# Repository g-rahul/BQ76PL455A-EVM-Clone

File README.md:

# BQ76PL455A-EVM-Clone
This respository contains low cost design files for BQ76PL455A-EVM Clone.

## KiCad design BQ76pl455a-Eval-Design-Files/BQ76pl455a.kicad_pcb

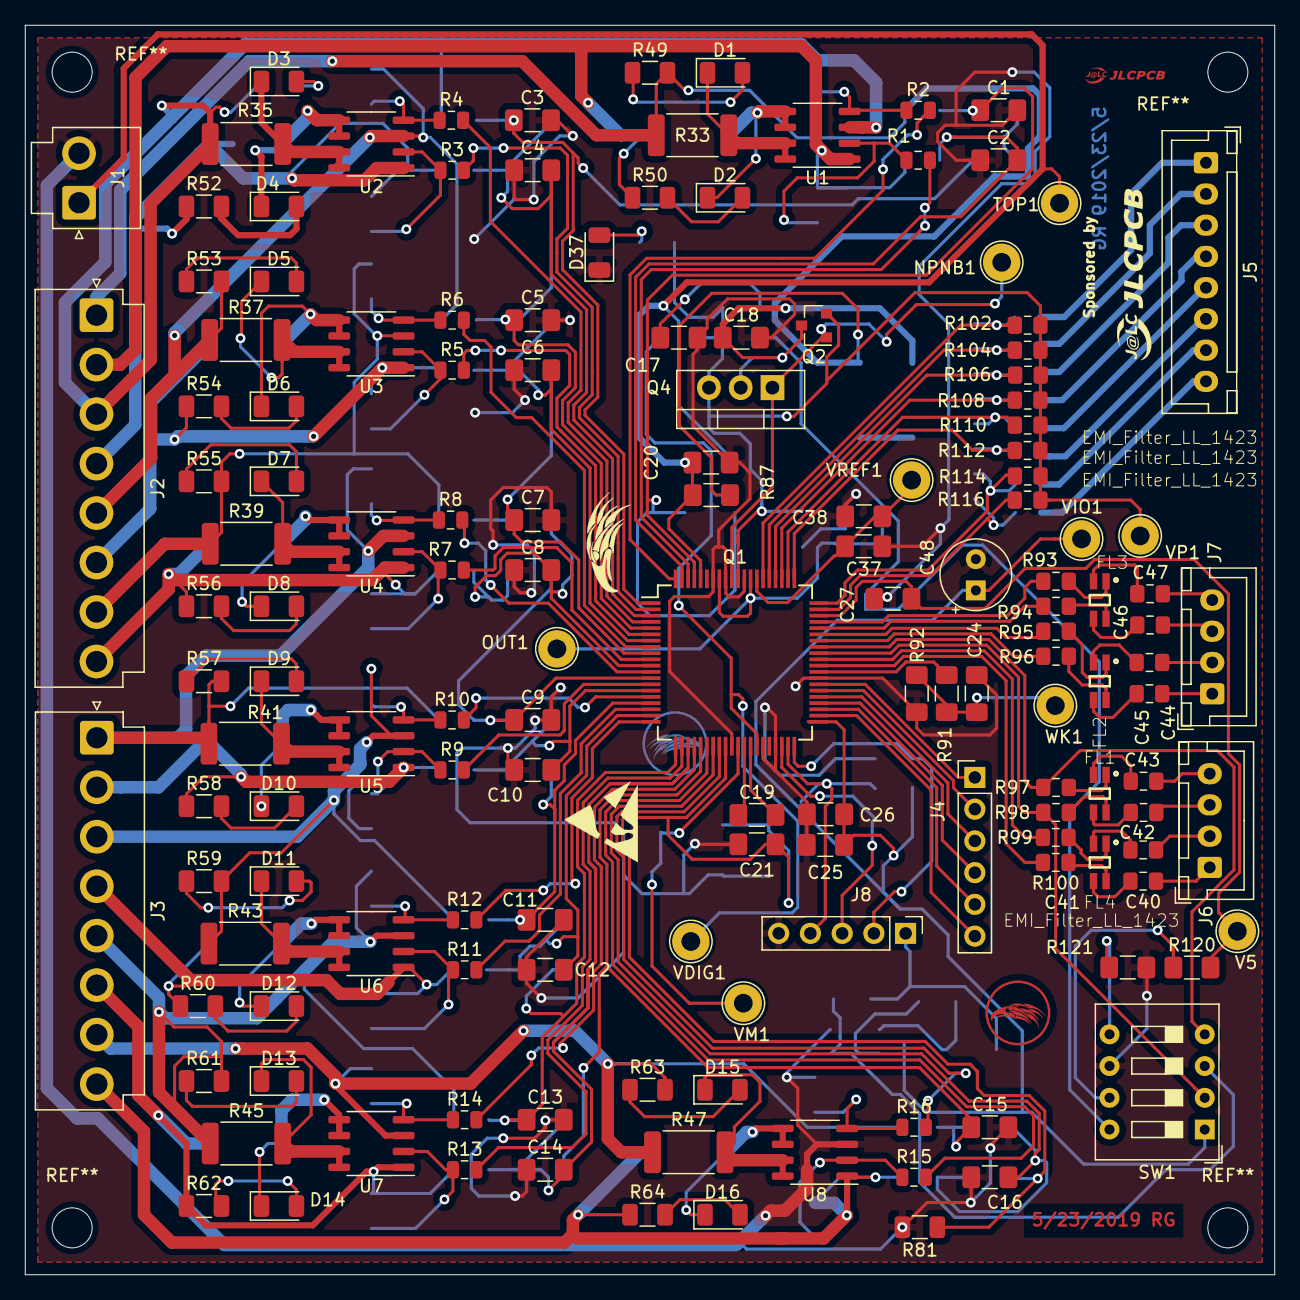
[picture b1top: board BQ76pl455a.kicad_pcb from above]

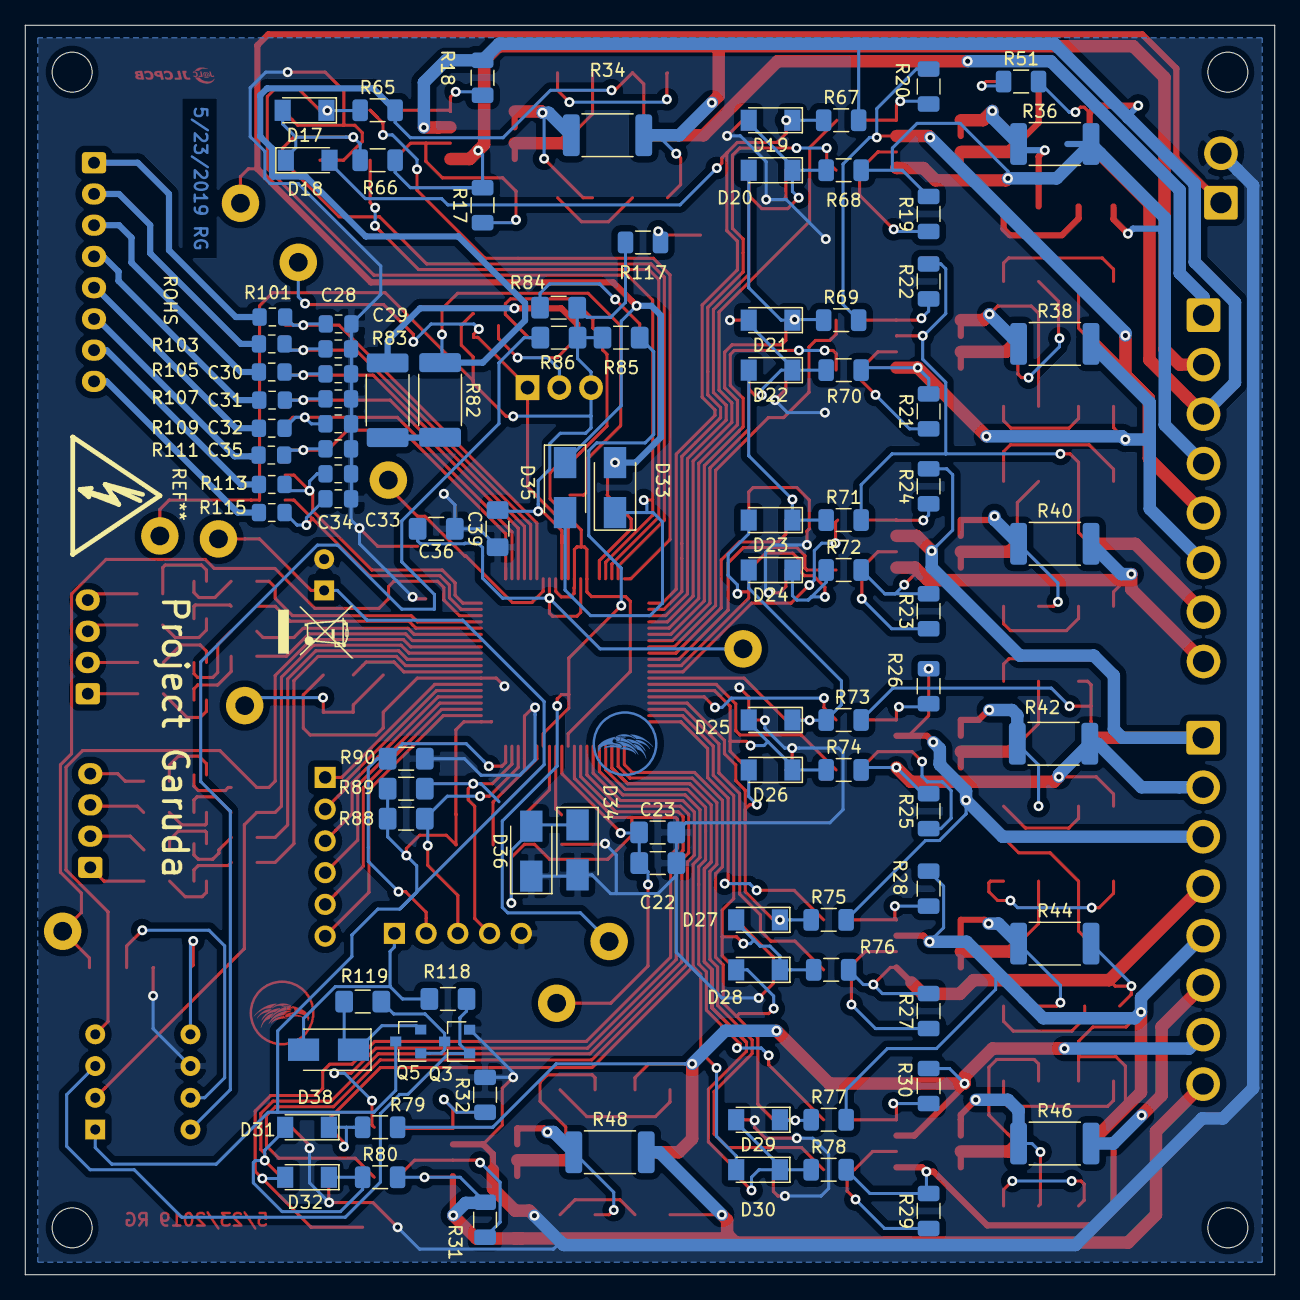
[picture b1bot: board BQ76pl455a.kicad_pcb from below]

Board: 2 copper layers, 100.0 x 100.0 mm, 243 parts (95 on the bottom side), 179 nets.

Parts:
C1, C2, C3, C4, C5, C6, C7, C8, C9, C10, C11, C12, C13, C14, C15, C16: C_Small; C_1206_3216Metric_Pad1.42x1.75mm_HandSolder
C17, C27: 4.7uF; C_1206_3216Metric_Pad1.42x1.75mm_HandSolder
C18, C19, C20, C21: 1uF; C_1206_3216Metric_Pad1.42x1.75mm_HandSolder
C22, C23: C; C_1206_3216Metric_Pad1.42x1.75mm_HandSolder
C24, C25, C26, C37, C38, C39: 0.1uF; C_1206_3216Metric_Pad1.42x1.75mm_HandSolder
C28, C29, C30, C31, C32, C33, C34, C35, C40, C41, C42, C43, C44, C45, C46, C47: 0.1uF; C_0805_2012Metric_Pad1.15x1.40mm_HandSolder
C36: 395pF; C_1206_3216Metric_Pad1.42x1.75mm_HandSolder
C48: CP; CP_Radial_Tantal_D5.5mm_P2.50mm
D1, D2, D3, D4, D5, D6, D7, D8, D9, D10, D11, D12, D13, D14, D15, D16, D37: LED; LED_1206_3216Metric
D17, D18, D19, D20, D21, D22, D23, D24, D25, D26, D27, D28, D29, D30, D31, D32: D_Zener_Small_ALT; D_MiniMELF
D33, D34, D35, D36, D38: MRA4007T3G; D_SMA
FL1, FL2, FL3, FL4: EMI_Filter_LL_1423; IND_744232090
J1: Conn_01x02_Male; JST_VH_B2P-VH-B_1x02_P3.96mm_Vertical
J2, J3: Conn_01x08_Male; JST_VH_B8P-VH-B_1x08_P3.96mm_Vertical
J4: Conn_01x06_Male; PinHeader_1x06_P2.54mm_Vertical
J5: Conn_01x08_Male; JST_XH_B8B-XH-A_1x08_P2.50mm_Vertical
J6, J7: Conn_01x04_Male; JST_XH_B4B-XH-A_1x04_P2.50mm_Vertical
J8: Conn_01x05_Male; PinHeader_1x05_P2.54mm_Vertical
NPNB1: TestPoint; TestPoint_Loop_D2.54mm_Drill1.5mm_Beaded
OUT1: TestPoint; TestPoint_Loop_D2.54mm_Drill1.5mm_Beaded
Q1: BQ76PL455A; TQFP-80_12x12mm_P0.5mm
Q2: MMBT5550L; SOT-23
Q3: ZXMN6A07F; SOT-23
Q4: MJE13007G; TO-220-3_Vertical
Q5: Si2319CDS; SOT-23
R1, R2, R3, R4, R5, R6, R7, R8, R9, R10, R11, R12, R13, R14, R15, R16: 2k; R_0805_2012Metric
R17, R18, R19, R20, R21, R22, R23, R24, R25, R26, R27, R28, R29, R30, R31, R32: 10k; R_1206_3216Metric
R33, R34, R35, R36, R37, R38, R39, R40, R41, R42, R43, R44, R45, R46, R47, R48: 10e; R_2512_6332Metric
R49, R50, R51, R52, R53, R54, R55, R56, R57, R58, R59, R60, R61, R62, R63, R64, R65, R66, R67, R68, R69, R70, R71, R72, R73, R74, R75, R76, R77, R78, R79, R80, R81, R117: 100; R_1206_3216Metric
R82, R83: 200; R_2512_6332Metric_Pad1.52x3.35mm_HandSolder
R84, R85, R86: 1; R_1206_3216Metric_Pad1.42x1.75mm_HandSolder
R87, R88, R89, R90, R91: 100; R_1206_3216Metric_Pad1.42x1.75mm_HandSolder
R92: 100K; R_1206_3216Metric_Pad1.42x1.75mm_HandSolder
R93, R94, R95, R96, R97, R98, R99, R100, R101, R102, R103, R104, R105, R106, R107, R108, R109, R110, R111, R112, R113, R114, R115, R116: 10; R_0805_2012Metric_Pad1.15x1.40mm_HandSolder
R118, R120, R121: 100k; R_1206_3216Metric_Pad1.42x1.75mm_HandSolder
R119: 50k; R_1206_3216Metric_Pad1.42x1.75mm_HandSolder
SW1: SW_DIP_x04; SW_DIP_SPSTx04_Slide_9.78x12.34mm_W7.62mm_P2.54mm
TOP1: TestPoint; TestPoint_Loop_D2.54mm_Drill1.5mm_Beaded
U1, U2, U3, U4, U5, U6, U7, U8: IRF7341; SO-8_3.9x4.9mm_P1.27mm
V5: TestPoint; TestPoint_Loop_D2.54mm_Drill1.5mm_Beaded
VDIG1: TestPoint; TestPoint_Loop_D2.54mm_Drill1.5mm_Beaded
VIO1: TestPoint; TestPoint_Loop_D2.54mm_Drill1.5mm_Beaded
VM1: TestPoint; TestPoint_Loop_D2.54mm_Drill1.5mm_Beaded
VP1: TestPoint; TestPoint_Loop_D2.54mm_Drill1.5mm_Beaded
VREF1: TestPoint; TestPoint_Loop_D2.54mm_Drill1.5mm_Beaded
WK1: TestPoint; TestPoint_Loop_D2.54mm_Drill1.5mm_Beaded

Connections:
A: FL4.2, R100.1
AGND1: C1.2, C2.1, C3.2, C4.1, C5.2, C6.1, C7.2, C8.1, C9.2, C10.1, C11.2, C12.1, C13.2, C14.1, C15.2, C16.1, C17.2, C18.2, C20.2, C21.1, C22.2, C23.2, C24.1, C25.1, C26.1, C27.2, C28.2, C29.2, C30.2, C31.2, C32.2, C33.2, C34.2, C35.2, C36.1, C37.1, C38.1, C39.1, C48.2, D34.2, D36.1, D37.1, J1.2, J8.5, Q1.30, Q1.35, Q1.37, Q1.48, Q1.69, Q1.72, Q1.74, Q3.2, R32.2, R81.2, R90.1, R92.2, R121.2, SW1.6, U8.3
AUX0: C28.1, Q1.66, R101.2, R102.1
AUX1: C29.1, Q1.65, R103.2, R104.1
AUX2: C30.1, Q1.64, R105.2, R106.1
AUX3: C31.1, Q1.63, R107.2, R108.1
AUX4: C32.1, Q1.62, R109.2, R110.1
AUX5: C33.1, Q1.61, R111.2, R112.1
AUX6: C34.1, Q1.60, R113.2, R114.1
AUX7: C35.1, Q1.59, R115.2, R116.1
B: FL4.1, R99.1
BAT1: J3.8, R31.2, R48.2, R64.1, R80.2, U8.1
BAT2: J3.7, R30.2, R47.1, R63.2, R79.2, U7.3
BAT3: J3.6, R29.2, R46.2, R62.1, R78.2, U7.1
BAT4: J3.5, R28.2, R45.1, R61.2, R77.2, U6.3
BAT5: J3.4, R27.2, R44.2, R60.1, R76.2, U6.1
BAT6: J3.3, R26.2, R43.1, R59.2, R75.2, U5.3
BAT7: J3.2, R25.2, R42.2, R58.1, R74.2, U5.1
BAT8: J3.1, R24.2, R41.1, R57.2, R73.2, U4.3
BAT9: J2.8, R23.2, R40.2, R56.1, R72.2, U4.1
BAT10: J2.7, R22.2, R39.1, R55.2, R71.2, U3.3
BAT11: J2.6, R21.2, R38.2, R54.1, R70.2, U3.1
BAT12: J2.5, R20.2, R37.1, R53.2, R69.2, U2.3
BAT13: J2.4, R19.2, R36.2, R52.1, R68.2, U2.1
BAT14: J2.3, R18.2, R35.1, R51.2, R67.2, U1.3
BAT15: J2.2, R17.2, R34.2, R50.1, R66.2, U1.1
BAT16: J2.1, R33.1, R49.2, R65.2, R82.1, R87.2
C: FL1.2, R98.1
CHM: C19.2, Q1.33
CHP: C19.1, Q1.32
COMMH+: Q1.55, R95.2
COMMH-: Q1.54, R96.2
COMML+: Q1.52, R98.2, SW1.2
COMML-: Q1.53, R97.2, SW1.4
D: FL1.1, R97.1
E: FL2.2, R96.1
EQ1: Q1.28, R16.2
EQ2: Q1.26, R15.2
EQ3: Q1.24, R14.2
EQ4: Q1.22, R13.2
EQ5: Q1.20, R12.2
EQ6: Q1.18, R11.2
EQ7: Q1.16, R10.2
EQ8: Q1.14, R9.2
EQ9: Q1.12, R8.2
EQ10: Q1.10, R7.2
EQ11: Q1.8, R6.2
EQ12: Q1.6, R5.2
EQ13: Q1.4, R4.2
EQ14: Q1.2, R3.2
EQ15: Q1.80, R2.2
EQ16: Q1.78, R1.2
F: FL2.1, R95.1
FAULTH+: Q1.57, R93.2
FAULTL+: Q1.50, R100.2
FAULTL-: Q1.51, R99.2
FAULT_H-: Q1.56, R94.2
FAULT_N: J8.2, Q1.40, R90.2
G: FL3.2, R94.1
GPIO0: J4.1, Q1.47
GPIO1: J4.2, Q1.46
GPIO2: J4.3, Q1.45
GPIO3: J4.4, Q1.44
GPIO4: J4.5, Q1.43
GPIO5: J4.6, Q1.42
H: FL3.1, R93.1
NPNB: NPNB1.1, Q1.71, Q2.1, Q4.1
unnamed: C17.1, R84.2
unnamed: C18.1, Q2.3, Q4.2, R83.2
unnamed: C40.1, J6.1
unnamed: C40.2, FL4.3
unnamed: C41.1, J6.2
unnamed: C41.2, FL4.4
unnamed: C42.1, J6.3
unnamed: C42.2, FL1.3
unnamed: C43.1, J6.4
unnamed: C43.2, FL1.4
unnamed: C44.1, J7.1
unnamed: C44.2, FL2.3
unnamed: C45.1, J7.2
unnamed: C45.2, FL2.4
unnamed: C46.1, J7.3
unnamed: C46.2, FL3.3
unnamed: C47.1, J7.4
unnamed: C47.2, FL3.4
unnamed: D1.1, R33.2, U1.7, U1.8
unnamed: D1.2, R49.1
unnamed: D2.1, R34.1, U1.5, U1.6
unnamed: D2.2, R50.2
unnamed: D3.1, R35.2, U2.7, U2.8
unnamed: D3.2, R51.1
unnamed: D4.1, R36.1, U2.5, U2.6
unnamed: D4.2, R52.2
unnamed: D5.1, R37.2, U3.7, U3.8
unnamed: D5.2, R53.1
unnamed: D6.1, R38.1, U3.5, U3.6
unnamed: D6.2, R54.2
unnamed: D7.1, R39.2, U4.7, U4.8
unnamed: D7.2, R55.1
unnamed: D8.1, R40.1, U4.5, U4.6
unnamed: D8.2, R56.2
unnamed: D9.1, R41.2, U5.7, U5.8
unnamed: D9.2, R57.1
unnamed: D10.1, R42.1, U5.5, U5.6
unnamed: D10.2, R58.2
unnamed: D11.1, R43.2, U6.7, U6.8
unnamed: D11.2, R59.1
unnamed: D12.1, R44.1, U6.5, U6.6
unnamed: D12.2, R60.2
unnamed: D13.1, R45.2, U7.7, U7.8
unnamed: D13.2, R61.1
unnamed: D14.1, R46.1, U7.5, U7.6
unnamed: D14.2, R62.2
unnamed: D15.1, R47.2, U8.7, U8.8
unnamed: D15.2, R63.1
unnamed: D16.1, R48.1, U8.5, U8.6
unnamed: D16.2, R64.2
unnamed: D37.2, R117.1
unnamed: D38.1, Q5.2, R119.2
unnamed: J5.1, R101.1
unnamed: J5.2, R103.1
unnamed: J5.3, R105.1
unnamed: J5.4, R107.1
unnamed: J5.5, R109.1
unnamed: J5.6, R111.1
unnamed: J5.7, R113.1
unnamed: J5.8, R115.1
unnamed: Q1.49, R91.1
unnamed: Q3.3, Q5.1, R119.1
unnamed: R1.1, R17.1, U1.2
unnamed: R10.1, R26.1, U5.4
unnamed: R11.1, R27.1, U6.2
unnamed: R12.1, R28.1, U6.4
unnamed: R13.1, R29.1, U7.2
unnamed: R14.1, R30.1, U7.4
unnamed: R15.1, R31.1, U8.2
unnamed: R16.1, R32.1, U8.4
unnamed: R2.1, R18.1, U1.4
unnamed: R3.1, R19.1, U2.2
unnamed: R4.1, R20.1, U2.4
unnamed: R5.1, R21.1, U3.2
unnamed: R6.1, R22.1, U3.4
unnamed: R7.1, R23.1, U4.2
unnamed: R8.1, R24.1, U4.4
unnamed: R9.1, R25.1, U5.2
unnamed: R82.2, R83.1
unnamed: R120.1, SW1.7
unnamed: R121.1, SW1.5
OUT1: C36.2, OUT1.1, Q1.68, Q1.73
RX: J8.4, Q1.39, R89.1
TOP: C20.1, D33.2, D35.1, J1.1, Q1.76, R87.1, TOP1.1
TX: J8.3, Q1.38, R88.1
V5VAO: C27.1, Q1.58, R120.2, V5.1
VCC: D38.2, J8.1, R118.2
VDIG: Q1.34, R85.2, VDIG1.1
VG: Q3.1, R118.1, SW1.3
VIO: C25.2, C26.2, C48.1, Q1.41, Q5.3, R88.2, R89.2, SW1.1, VIO1.1
VIOREG: R86.2, SW1.8
VM: C22.1, C23.1, Q1.31, VM1.1
VP: C39.2, Q1.70, Q2.2, Q4.3, R84.1, R85.1, R86.1, R102.2, R104.2, R106.2, R108.2, R110.2, R112.2, R114.2, R116.2, R117.2, VP1.1
VREF: C37.2, C38.2, Q1.67, VREF1.1
VSENSE0: C21.2, D32.2, D34.1, D36.2, Q1.29, R81.1
VSENSE1: C16.2, D31.2, D32.1, Q1.27, R80.1
VSENSE2: C15.1, D30.2, D31.1, Q1.25, R79.1
VSENSE3: C14.2, D29.2, D30.1, Q1.23, R78.1
VSENSE4: C13.1, D28.2, D29.1, Q1.21, R77.1
VSENSE5: C12.2, D27.2, D28.1, Q1.19, R76.1
VSENSE6: C11.1, D26.2, D27.1, Q1.17, R75.1
VSENSE7: C10.2, D25.2, D26.1, Q1.15, R74.1
VSENSE8: C9.1, D24.2, D25.1, Q1.13, R73.1
VSENSE9: C8.2, D23.2, D24.1, Q1.11, R72.1
VSENSE10: C7.1, D22.2, D23.1, Q1.9, R71.1
VSENSE11: C6.2, D21.2, D22.1, Q1.7, R70.1
VSENSE12: C5.1, D20.2, D21.1, Q1.5, R69.1
VSENSE13: C4.2, D19.2, D20.1, Q1.3, R68.1
VSENSE14: C3.1, D18.2, D19.1, Q1.1, R67.1
VSENSE15: C2.2, D17.2, D18.1, Q1.79, R66.1
VSENSE16: C1.1, D17.1, D33.1, D35.2, Q1.77, R65.1
WAKEUP: C24.2, R91.2, R92.1, WK1.1

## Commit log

2020-07-31 second
